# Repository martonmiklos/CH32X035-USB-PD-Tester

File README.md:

### What?

[This is the clone of this project](https://github.com/wagiminator/CH32X035-USB-PD-Tester)

Differences:
- Kicad 7+ (instead EasyEda)
- More generic pushbuttons
- Added programmer header
- Added load switch (for testing purposes)
- Changed voltage regulator to 3V3 as the
- Adoptable for LCDs with different pinouts (some exists with swapped GND and VDD pins)

DO NOT BUILD IT YET. Mahor fuckups discovered during board bringup:
- The voltage regulator is not capable of supplying enought current to the LVD

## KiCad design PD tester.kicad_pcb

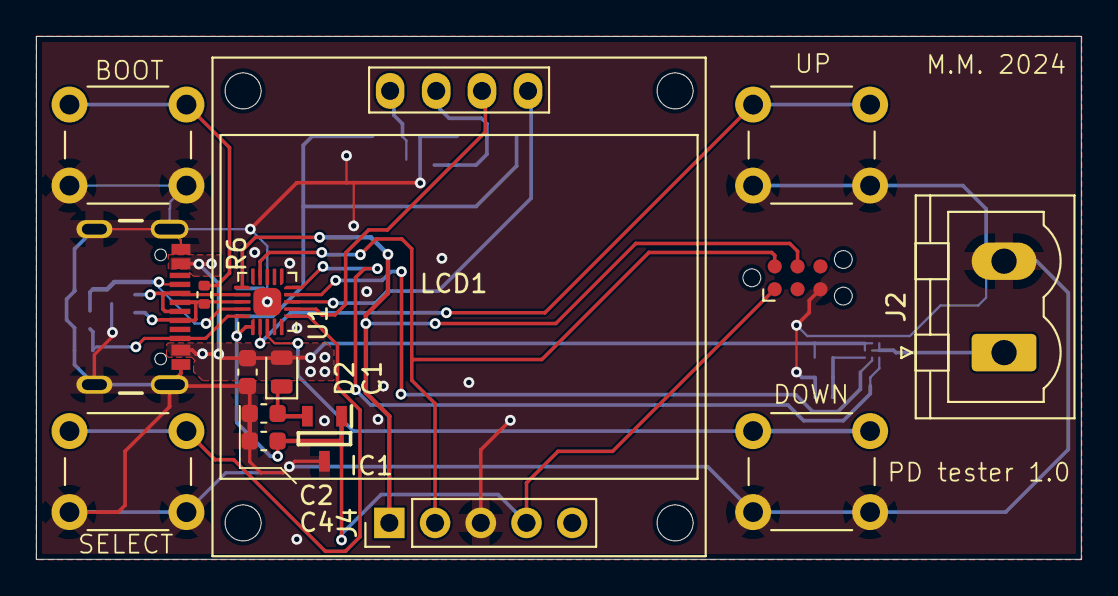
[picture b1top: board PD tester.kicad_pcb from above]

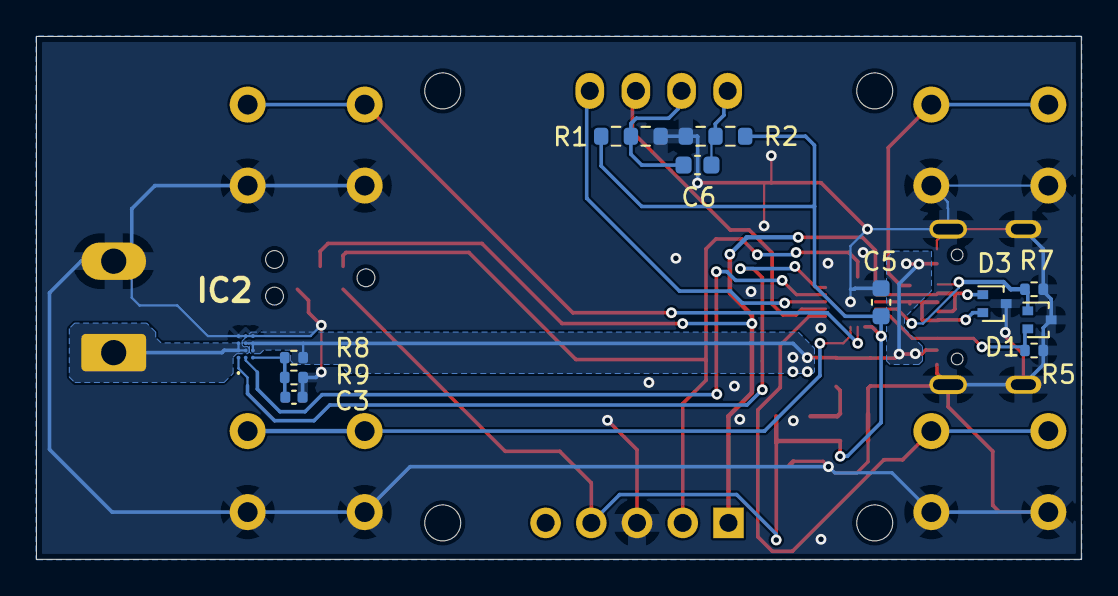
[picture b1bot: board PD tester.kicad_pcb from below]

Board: 2 copper layers, 58.0 x 29.1 mm, 28 parts (12 on the bottom side), 22 nets.

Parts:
C1, C2: 1uF; C_0603_1608Metric
C3: TBD; C_0402_1005Metric
C4, C6: 100nF; C_0603_1608Metric
C5: 4,7uF; C_0603_1608Metric
D1, D3: SM15.TCT; SOT-416
D2: MCL4148; D_MicroMELF
IC1: TS78L03CX_RFG; SOT95P275X135-3N
IC2: FPF3380UCX
J1: USB4105-GF-A; GCT_USB4105-GF-A_1
J2: Screw_Terminal_01x02; PhoenixContact_MSTBVA_2,5_2-G-5,08_1x02_P5.08mm_Vertical
J3: TC2030-NL; Tag-Connect_TC2030-IDC-NL_2x03_P1.27mm_Vertical
J4: WCH link; PinHeader_1x05_P2.54mm_Vertical
LCD1: SSD1306; 128x64OLED_mounting_holes
R1, R2: R_0603_1608Metric_popopt
R5, R7: 5K1; R_0402_1005Metric
R6: 1K; R_0402_1005Metric
R8: 82K; R_0402_1005Metric
R9: 4K3; R_0402_1005Metric
SW_BOOT1: SW_Push_Dual; SW_PUSH_6mm
SW_DOWN1: SW_Push_Dual; SW_PUSH_6mm
SW_SELECT1: SW_Push_Dual; SW_PUSH_6mm
SW_UP1: SW_Push_Dual; SW_PUSH_6mm
U1: CH32X035F8U6; UQFN-20_3x3mm_P0.4mm_w_ep

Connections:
+3.3V: C4.1, C5.1, IC1.1 (OUT), J3.1 (VCC), J4.4, R1.3, R2.3, U1.1 (VDD)
/CC1: D1.1 (K1), J1.A5 (CC1), R7.1, U1.19 (PC14)
/CC2: D1.2 (K2), J1.B5 (CC2), R5.1, U1.20 (PC15)
/OVLO: C3.1, IC2.C1 (OVLO), R8.2, R9.1
/USB_DN: D3.1 (K1), J1.A7 (DN1), J1.B7 (DN2), U1.17 (PC16)
/VIN: C1.1, D2.2 (A), IC2.B3 (IN), IC2.C2 (IN), IC2.C3 (IN), J1.A4_B9 (VBUS), J1.B4_A9 (VBUS), R8.1
/VOUT: IC2.A2 (OUT), IC2.A3 (OUT), IC2.B2 (OUT), J2.1
DOWN: SW_DOWN1.1, U1.3 (PA1)
GND: C1.2, C2.2, C3.2, C4.2, C5.2, D1.3 (A), D3.3 (A), IC1.3 (GND), IC2.A4 (GND), IC2.B4 (GND), IC2.C4 (GND), J1.A1_B12 (GND), J1.B1_A12 (GND), J1.S1 (SHELL_GND), J1.S2 (SHELL_GND), J1.S3 (SHELL_GND), J1.S4 (SHELL_GND), J2.2, J3.5 (GND), J4.3, R1.1, R2.1, R5.2, R7.2, R9.2, SW_BOOT1.2, SW_DOWN1.2, SW_SELECT1.2, SW_UP1.2, U1.PAD (GND)
unnamed: C2.1, D2.1 (K), IC1.2 (IN)
unnamed: C6.2, LCD1.1 (GND), R2.2
unnamed: C6.1, LCD1.2 (VCC), R1.2
unnamed: R6.2, SW_BOOT1.1
SCL: LCD1.3 (SCL), U1.7 (PA5)
SDA: LCD1.4 (SDA), U1.8 (PA6)
SELECT: SW_SELECT1.1, U1.6 (PA4)
SWDCLK: J3.4 (SWCLK), J4.1, U1.16 (PC19)
SWDIO: J3.2 (SWDIO), J4.2, U1.14 (PC18)
UP: SW_UP1.1, U1.2 (PA0)
USB_DP: D3.2 (K2), J1.A6 (DP1), J1.B6 (DP2), R6.1, U1.18 (PC17)
~ENB: IC2.A1 (~ENB), U1.10 (PB0)
~VIN_OK: IC2.B1 (ACOKB), U1.9 (PA7)

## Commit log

2024-06-28 Repo init
2024-06-28 Add README
2024-06-28 Pimp readme
